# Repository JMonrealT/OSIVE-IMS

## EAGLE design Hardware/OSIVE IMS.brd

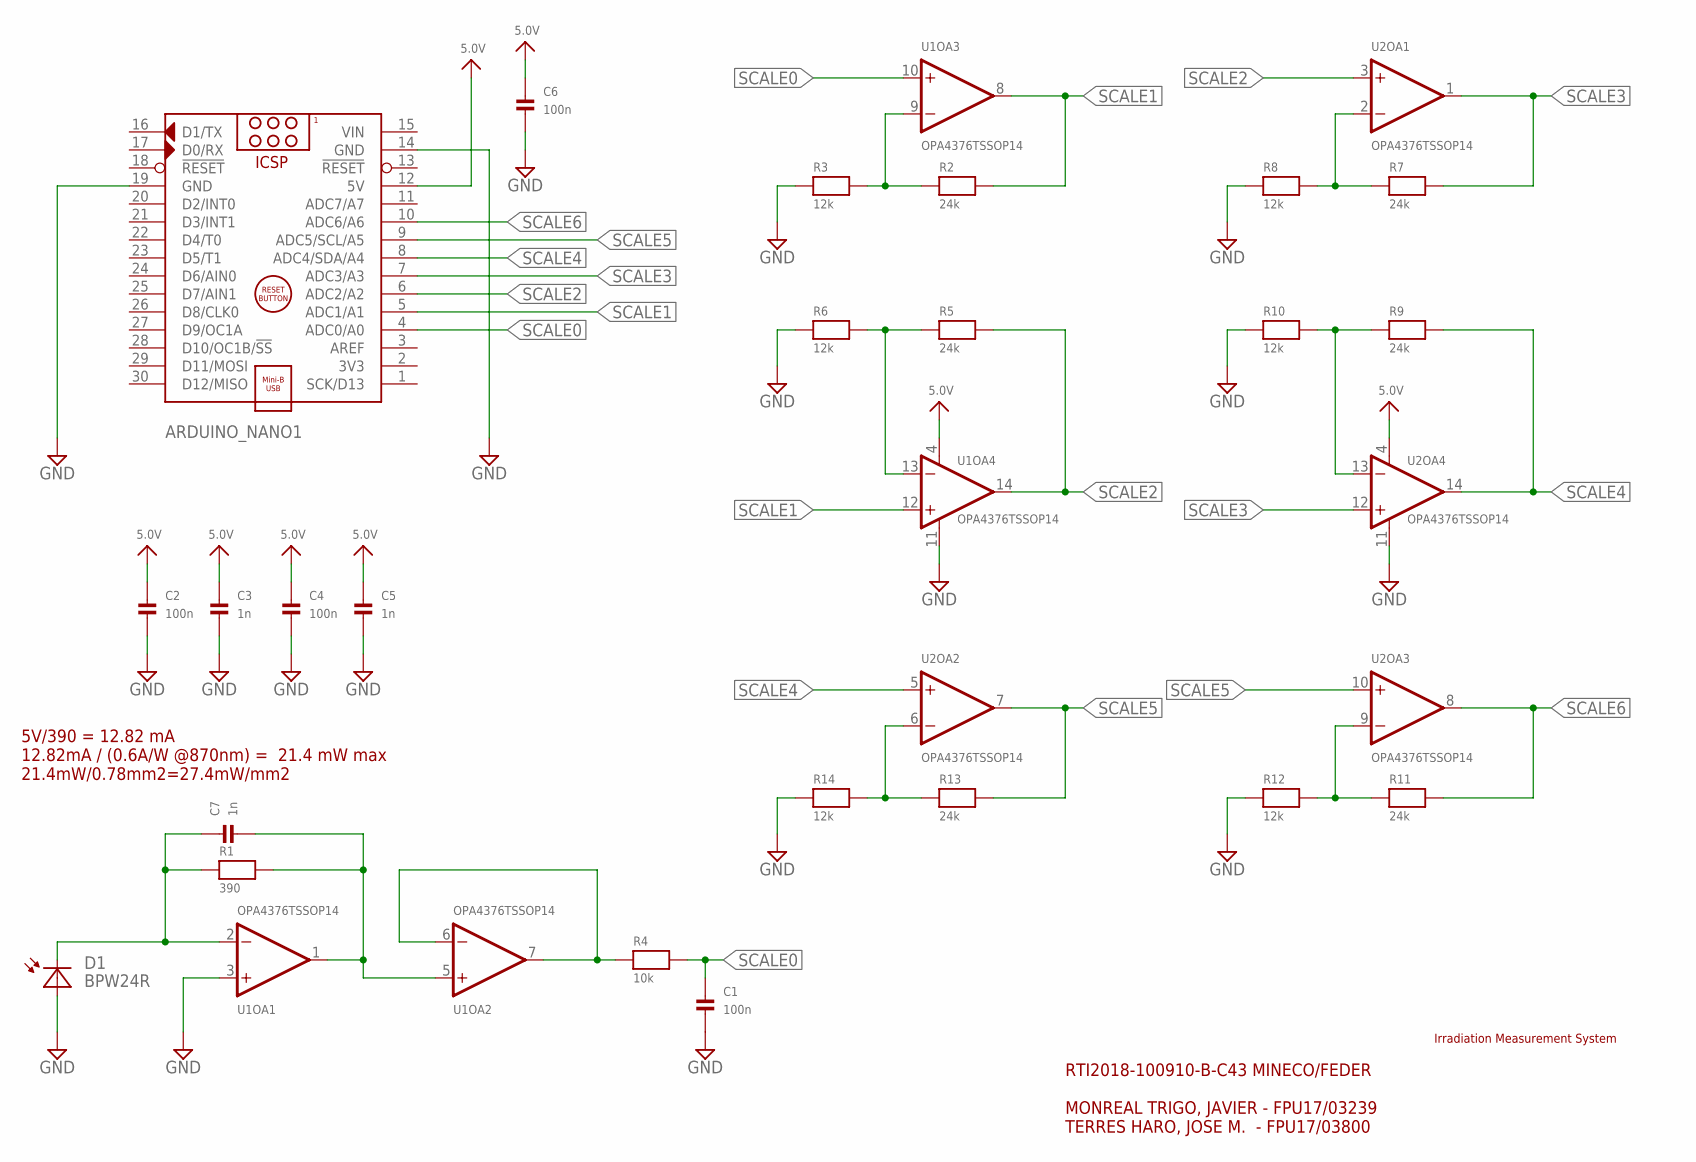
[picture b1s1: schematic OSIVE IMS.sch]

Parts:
ARDUINO_NANO1: ARDUINO_NANO
C1, C2, C4, C6: 100n; 0805
C3, C5, C7: 1n; 0805
D1: BPW24R; TO-18
R1: 390; 0805
R2, R5, R7, R9, R11, R13: 24k; 0805
R3, R6, R8, R10, R12, R14: 12k; 0805
R4: 10k; 0805
U1, U2: OPA4376TSSOP14; TSSOP14-NOTHERMALPAD

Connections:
5.0V: ARDUINO_NANO1.12 (5V), C2.1, C3.1, C4.1, C5.1, C6.1, U1.4 (V+), U2.4 (V+)
DSNFOJW: R4.1, U1.6 (-IN), U1.7 (OUT)
GND: ARDUINO_NANO1.14 (GND), ARDUINO_NANO1.19 (GND), C1.2, C2.2, C3.2, C4.2, C5.2, C6.2, D1.A, R3.1, R6.1, R8.1, R10.1, R12.1, R14.1, U1.3 (+IN), U1.11 (V-), U2.11 (V-)
unnamed: C7.1, D1.K (C), R1.1, U1.2 (-IN)
unnamed: R2.1, R3.2, U1.9 (-IN)
unnamed: C7.2, R1.2, U1.1 (OUT), U1.5 (+IN)
unnamed: R7.1, R8.2, U2.2 (-IN)
unnamed: R5.1, R6.2, U1.13 (-IN)
unnamed: R9.1, R10.2, U2.13 (-IN)
unnamed: R11.1, R12.2, U2.9 (-IN)
unnamed: R13.1, R14.2, U2.6 (-IN)
SCALE0: ARDUINO_NANO1.4 (ADC0/A0), C1.1, R4.2, U1.10 (+IN)
SCALE1: ARDUINO_NANO1.5 (ADC1/A1), R2.2, U1.8 (OUT), U1.12 (+IN)
SCALE2: ARDUINO_NANO1.6 (ADC2/A2), R5.2, U1.14 (OUT), U2.3 (+IN)
SCALE3: ARDUINO_NANO1.7 (ADC3/A3), R7.2, U2.1 (OUT), U2.12 (+IN)
SCALE4: ARDUINO_NANO1.8 (ADC4/SDA/A4), R9.2, U2.5 (+IN), U2.14 (OUT)
SCALE5: ARDUINO_NANO1.9 (ADC5/SCL/A5), R13.2, U2.7 (OUT), U2.10 (+IN)
SCALE6: ARDUINO_NANO1.10 (ADC6/A6), R11.2, U2.8 (OUT)
VIN: ARDUINO_NANO1.15 (VIN)

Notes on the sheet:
RTI2018-100910-B-C43 MINECO/FEDER MONREAL TRIGO, JAVIER - FPU17/03239 TERRES HARO, JOSE M. - FPU17/03800
Irradiation Measurement System
5V/390 = 12.82 mA 12.82mA / (0.6A/W @870nm) = 21.4 mW max 21.4mW/0.78mm2=27.4mW/mm2

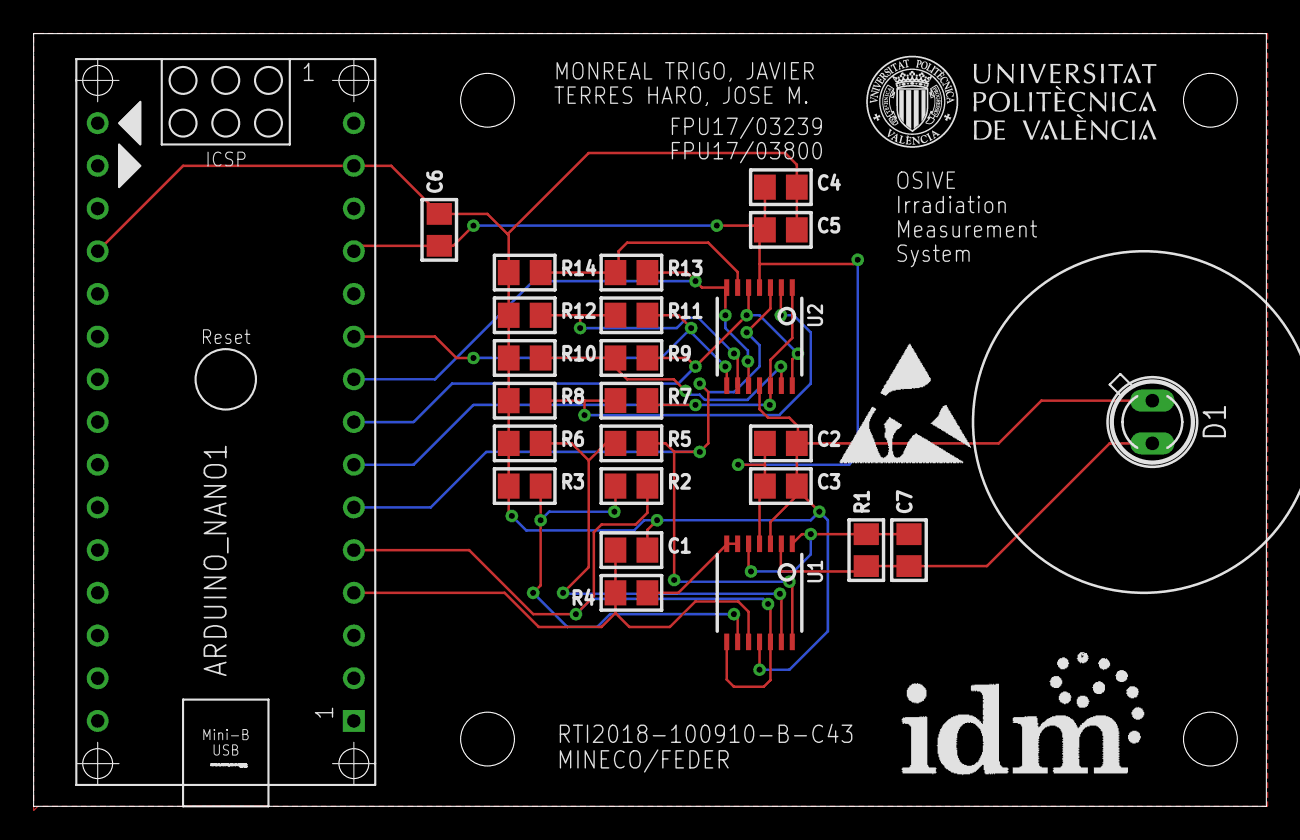
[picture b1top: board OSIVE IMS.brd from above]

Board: 2 copper layers, 73.3 x 46.0 mm, 25 parts (0 on the bottom side), 18 nets.

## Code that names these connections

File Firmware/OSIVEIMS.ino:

unsigned int SCALE0 = 0;
unsigned int SCALE1 = 0;
unsigned int SCALE2 = 0;
unsigned int SCALE3 = 0;
unsigned int SCALE4 = 0;
unsigned int SCALE5 = 0;
unsigned int SCALE6 = 0;
char sendStr[40]; 

void setup() {
  Serial.begin(9600);
}

void loop() {
  SCALE0 = 0;
  SCALE1 = 0;
  SCALE2 = 0;
  SCALE3 = 0;
  SCALE4 = 0;
  SCALE5 = 0;
  SCALE6 = 0;
  int nAvg = 64;
  for(int i = 0; i<nAvg; i++)
  {
    analogRead(A0);
    SCALE0 += analogRead(A0);
    analogRead(A6); 
    SCALE6 += analogRead(A6); 
    analogRead(A1); 
    SCALE1 += analogRead(A1);  
    analogRead(A5);  
    SCALE5 += analogRead(A5);    
    analogRead(A2); 
    SCALE2 += analogRead(A2); 
    analogRead(A4);   
    SCALE4 += analogRead(A4);   
    analogRead(A3);  
    SCALE3 += analogRead(A3);
  }
  SCALE0 /= nAvg;
  SCALE1 /= nAvg;
  SCALE2 /= nAvg;
  SCALE3 /= nAvg;
  SCALE4 /= nAvg;
  SCALE5 /= nAvg;
  SCALE6 /= nAvg;
  sprintf(sendStr,"Data:%04d;%04d;%04d;%04d;%04d;%04d;%04d\n",SCALE0,SCALE1,SCALE2,SCALE3,SCALE4,SCALE5,SCALE6);
  Serial.print(sendStr);
  /*
  Serial.print(SCALE0); // 27.4 mW/mm2
  Serial.print(";"); 
  Serial.print(SCALE1); // 9.13 mW/mm2
  Serial.print(";");
  Serial.print(SCALE2); // 3.04 mW/mm2
  Serial.print(";");
  Serial.print(SCALE3); // 1.01 mW/mm2 = 101 mW/cm2
  Serial.print(";");
  Serial.print(SCALE4); // 33.8 mW/cm2
  Serial.print(";");
  Serial.print(SCALE5); // 11.3 mW/cm2
  Serial.print(";");
  Serial.println(SCALE6); // 3.8 mW/cm2
  */
  delay(1000);
}

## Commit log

2023-02-21 CC BY-NC-SA LICENSE
    CC BY-NC-SA
    This license allows reusers to distribute, remix, adapt, and build upon the material in any medium or format for noncommercial purposes only, and only so long as attribution is given to the creator. 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
    For commercial permissions contact: jmonreal@upv.es
2024-09-23 Files added

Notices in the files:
parts and their libraries:
microbuilder: This work is placed in the public domain, and may be freely used for commercial and non-commercial work with the following conditions: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
